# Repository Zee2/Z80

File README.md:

# Z80
Z80-computer-on-a-breadboard utilities, scripts, and assets

uart.ino - Software-defined serial UART for the Z80 project

eepromFlash.ino - EEPROM flasher for the AT28C64 used for the system ROM

binaryWriter.py - PC-side utility for the EEPROM flasher

jumptest.asm - Test Z80 assembler code

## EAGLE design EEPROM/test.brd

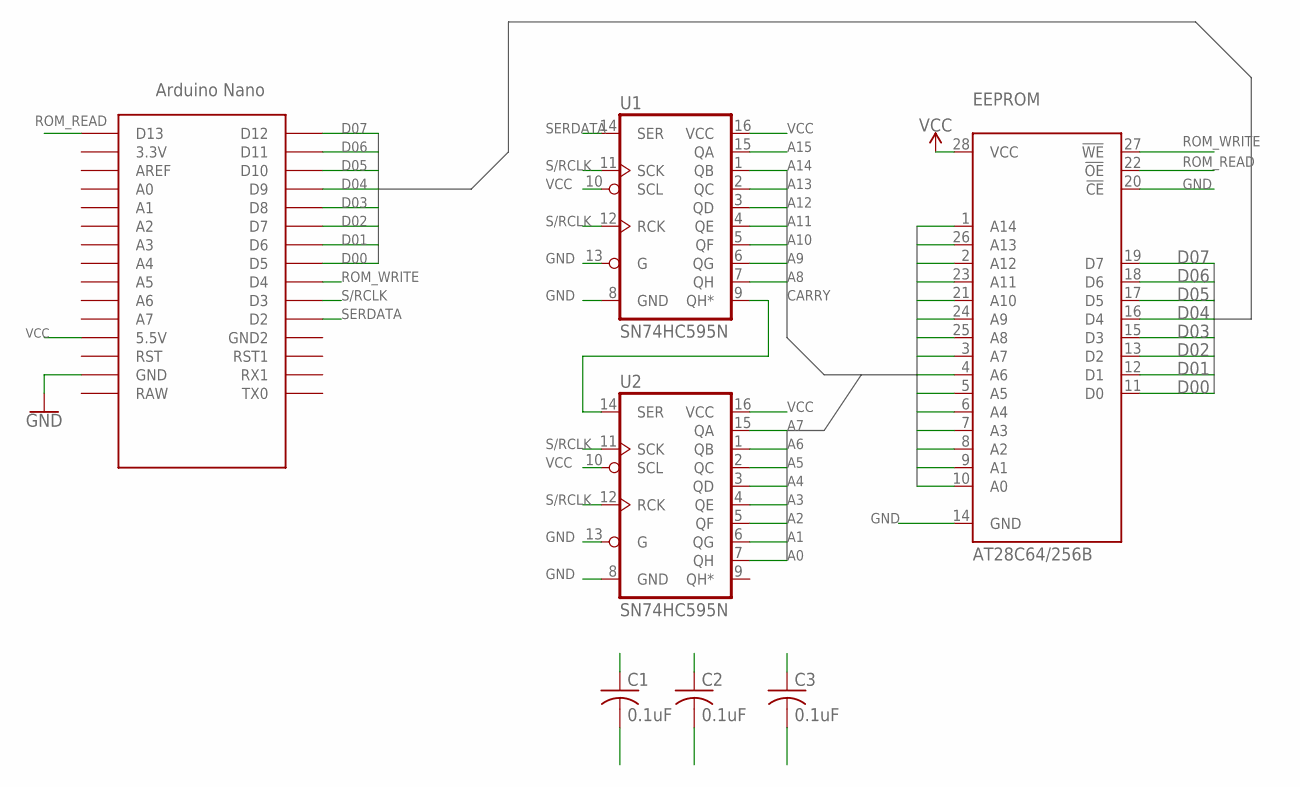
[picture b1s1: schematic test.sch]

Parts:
C1, C2, C3: 0.1uF; C025-030X050
EEPROM: AT28C64/256B; DIL28-6
U1, U2: SN74HC595N; DIP16
U$1: NANO

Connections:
A0: EEPROM.10 (A0), U2.7 (QH)
A1: EEPROM.9 (A1), U2.6 (QG)
A2: EEPROM.8 (A2), U2.5 (QF)
A3: EEPROM.7 (A3), U2.4 (QE)
A4: EEPROM.6 (A4), U2.3 (QD)
A5: EEPROM.5 (A5), U2.2 (QC)
A6: EEPROM.4 (A6), U2.1 (QB)
A7: EEPROM.3 (A7), U2.15 (QA)
A8: EEPROM.25 (A8), U1.7 (QH)
A9: EEPROM.24 (A9), U1.6 (QG)
A10: EEPROM.21 (A10), U1.5 (QF)
A11: EEPROM.23 (A11), U1.4 (QE)
A12: EEPROM.2 (A12), U1.3 (QD)
A13: EEPROM.26 (A13), U1.2 (QC)
A14: EEPROM.1 (A14), U1.1 (QB)
A15: U1.15 (QA)
CARRY: U1.9 (QH*), U2.14 (SER)
D00: EEPROM.11 (D0), U$1.D5
D01: EEPROM.12 (D1), U$1.D6
D02: EEPROM.13 (D2), U$1.D7
D03: EEPROM.15 (D3), U$1.D8
D04: EEPROM.16 (D4), U$1.D9
D05: EEPROM.17 (D5), U$1.D10
D06: EEPROM.18 (D6), U$1.D11
D07: EEPROM.19 (D7), U$1.D12
GND: C1.2, C2.2, C3.2, EEPROM.14 (GND), EEPROM.20 (!CE), U1.8 (GND), U1.13 (G), U2.8 (GND), U2.13 (G), U$1.GND
ROM_READ: EEPROM.22 (!OE), U$1.D13
ROM_WRITE: EEPROM.27 (!WE), U$1.D4
S/RCLK: U1.11 (SCK), U1.12 (RCK), U2.11 (SCK), U2.12 (RCK), U$1.D3
SERDATA: U1.14 (SER), U$1.D2
VCC: C1.1, C2.1, C3.1, EEPROM.28 (VCC), U1.10 (SCL), U1.16 (VCC), U2.10 (SCL), U2.16 (VCC), U$1.5V (5.5V)

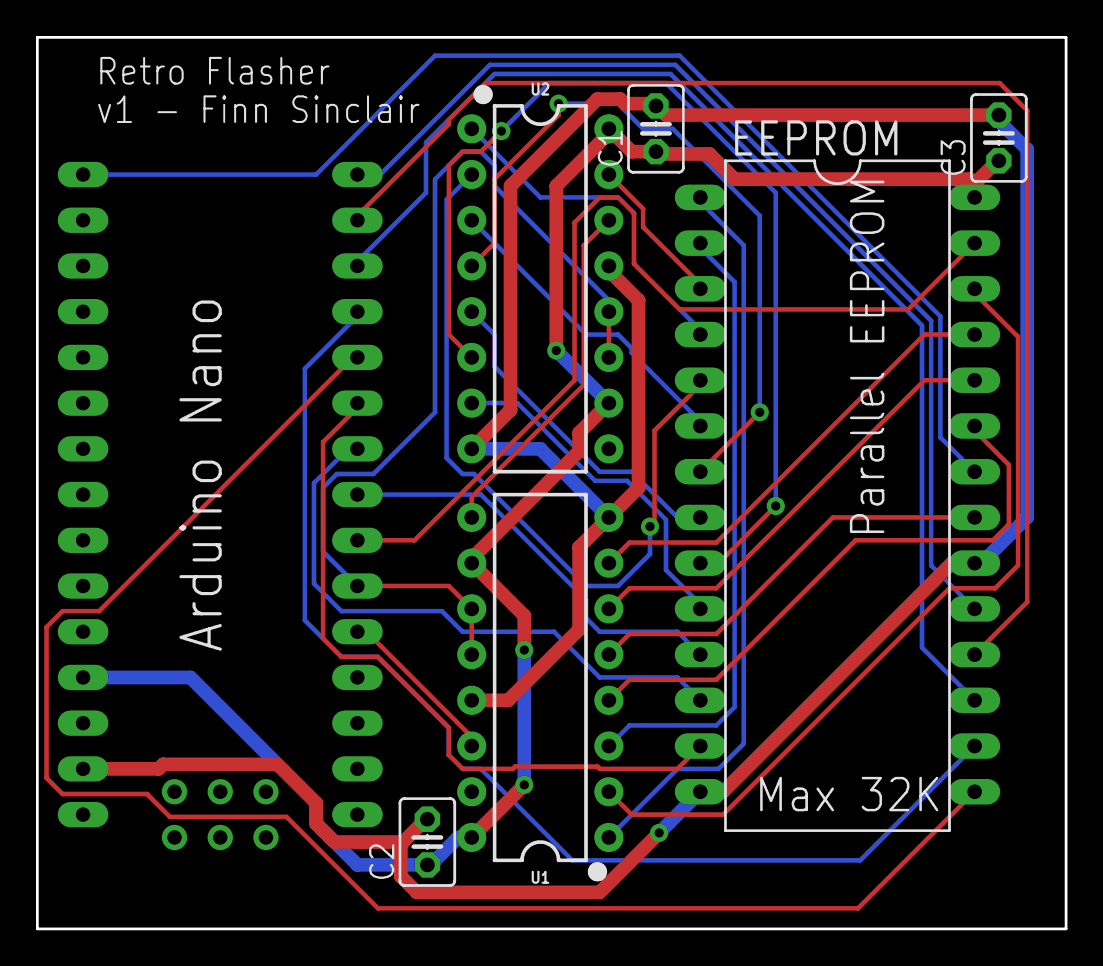
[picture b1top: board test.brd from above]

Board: 2 copper layers, 57.1 x 49.5 mm, 7 parts (0 on the bottom side), 30 nets.

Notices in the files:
parts and their libraries:
SparkFun-IC-Logic: Licensing: Creative Commons ShareAlike 4.0 International - https://creativecommons.org/licenses/by-sa/4.0
